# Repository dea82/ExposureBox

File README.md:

# ExposureBox
AVR based exposure box system

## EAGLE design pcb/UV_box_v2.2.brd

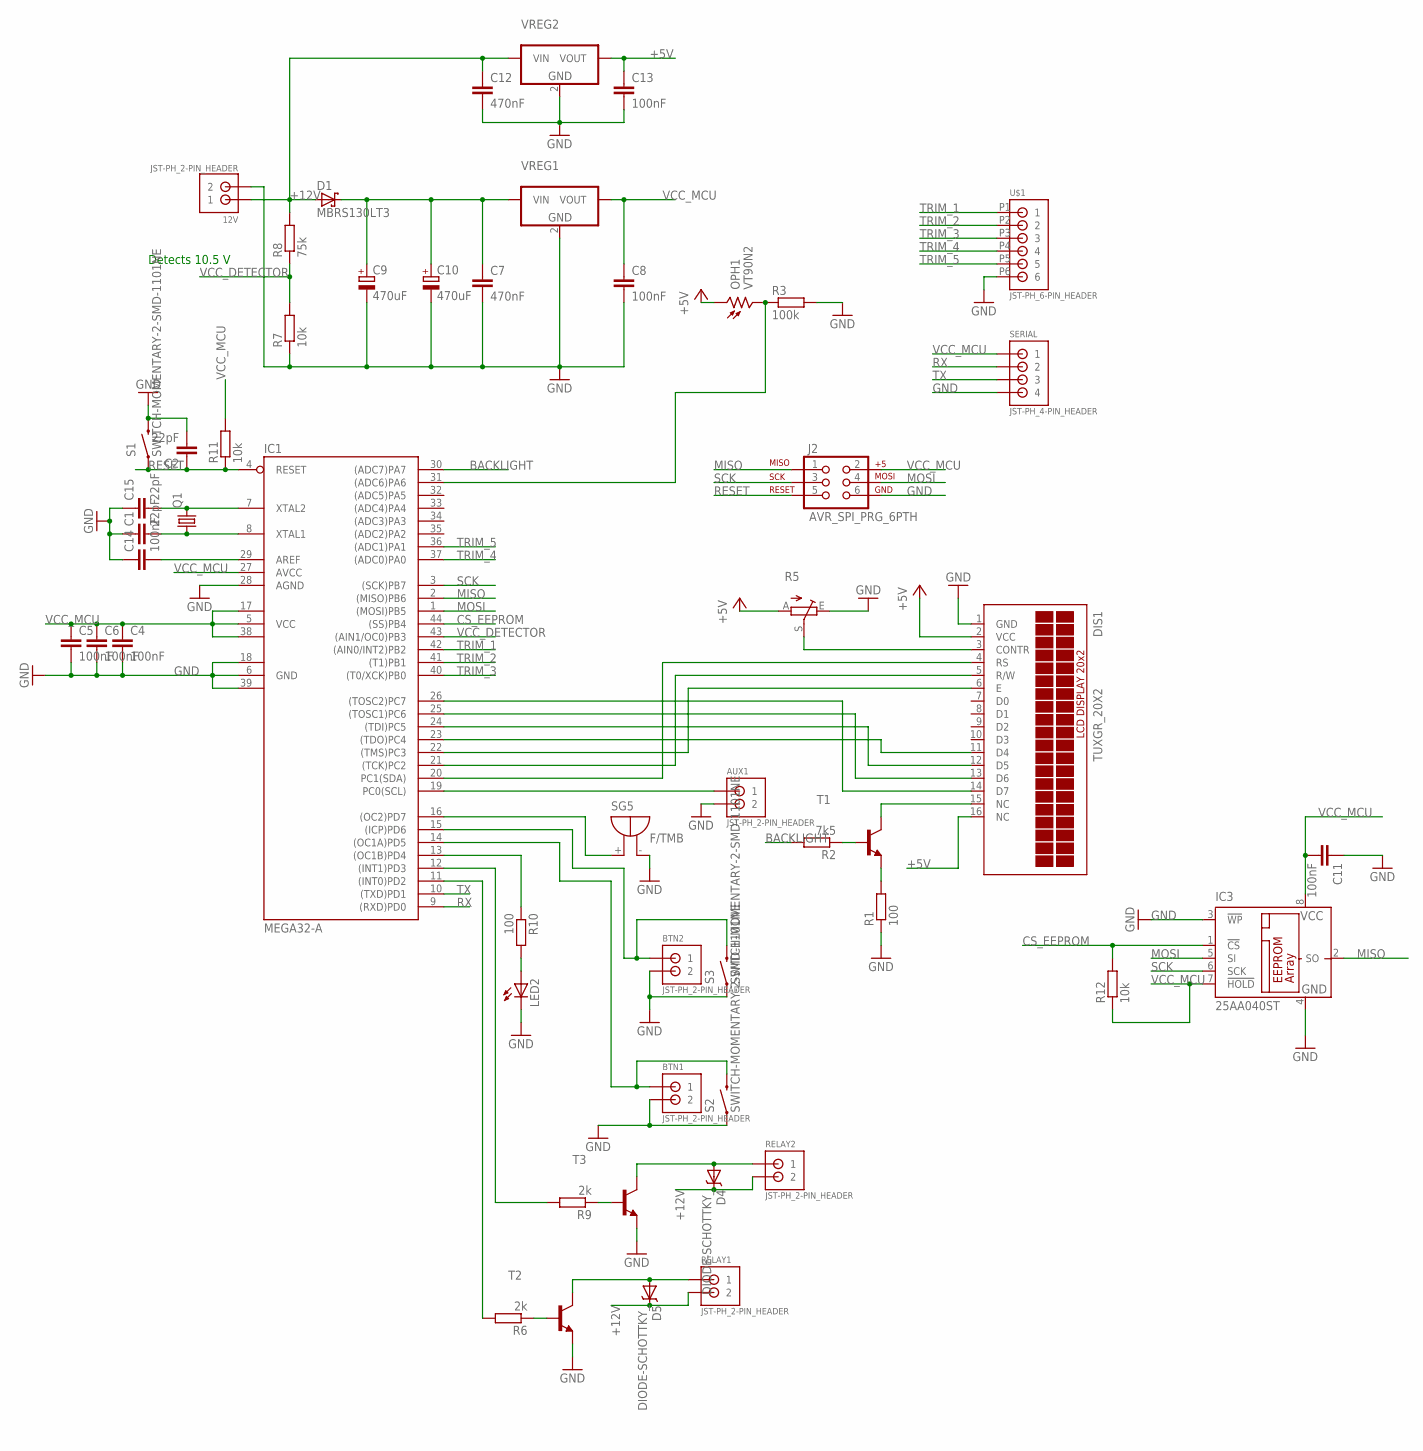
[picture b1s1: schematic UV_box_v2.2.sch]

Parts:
12V: JST-PH_2-PIN_HEADER; JST_B2B-PH_HEADER
AUX1: JST-PH_2-PIN_HEADER; JST_B2B-PH_HEADER
BTN1, BTN2: JST-PH_2-PIN_HEADER; JST_B2B-PH_HEADER
C1, C2, C15: 22pF; C0805
C4, C5, C6, C8, C11, C13, C14: 100nF; C0805
C7, C12: 470nF; C0805
C9, C10: 470uF; 140CLH-0810
D1: MBRS130LT3; SMB
D4, D5: DIODE-SCHOTTKY_; SMA-DIODE
DIS1: TUXGR_20X2
IC1: MEGA32-A; TQFP44
IC3: 25AA040ST; TSSOP8
J2: AVR_SPI_PRG_6PTH; 2X3
LED2: LEDCHIPLED_0805; CHIPLED_0805
OPH1: VT90N2; VT900
Q1: CRYSTALHC49S; HC49/S
R1: 100; R1206
R2: 7k5; R1206
R3: 100k; R1206
R5: TRIM_EU-B25P; B25P
R6, R9: 2k; R1206
R7, R11, R12: 10k; R1206
R8: 75k; R1206
R10: 100; R0805
RELAY1, RELAY2: JST-PH_2-PIN_HEADER; JST_B2B-PH_HEADER
S1, S2, S3: SWITCH-MOMENTARY-2-SMD-1101NE; TACTILE-SWITCH-1101NE
SERIAL: JST-PH_4-PIN_HEADER; JST_B4B-PH_HEADER
SG5: F/TMB
T1, T2, T3: BC847B-NPN-SOT23-BEC; SOT23-BEC
U$1: JST-PH_6-PIN_HEADER; JST_B6B-PH_HEADER
VREG1, VREG2: VREG_3PINS-D2PAK; D2PAK

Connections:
+5V: C13.1, DIS1.2 (VCC), DIS1.16 (NC), OPH1.1, R5.A, VREG2.3 (VOUT)
+12V: 12V.P1 (1), C12.1, D1.A, D4.C, D5.C, R8.2, RELAY1.P2 (2), RELAY2.P2 (2), VREG2.1 (VIN)
BACKLIGHT: IC1.30 ((ADC7)PA7), R2.2
CS_EEPROM: IC1.44 ((SS)PB4), IC3.1 (!CS), R12.2
GND: 12V.P2 (2), AUX1.P2 (2), BTN1.P2 (2), BTN2.P2 (2), C1.1, C2.2, C4.2, C5.2, C6.2, C7.2, C8.2, C9.-, C10.-, C11.1, C12.2, C13.2, C14.1, C15.1, DIS1.1 (GND), IC1.6 (GND), IC1.18 (GND1), IC1.28 (AGND), IC1.39 (GND2), IC3.3 (!WP), IC3.4 (GND), J2.6, LED2.C, R1.1, R3.2, R5.E, R7.1, S1.P$2 (2), S2.P$1 (1), S3.P$1 (1), SERIAL.P4 (4), SG5.-, T2.E, T3.E, U$1.P6 (6), VREG1.2 (GND), VREG2.2 (GND)
MISO: IC1.2 ((MISO)PB6), IC3.2 (SO), J2.1
MOSI: IC1.1 ((MOSI)PB5), IC3.5 (SI), J2.4
unnamed: R1.2, T1.E
unnamed: DIS1.15 (NC), T1.C
unnamed: DIS1.3 (CONTR), R5.S
unnamed: R2.1, T1.B
unnamed: DIS1.4 (RS), IC1.20 (PC1(SDA))
unnamed: DIS1.5 (R/W), IC1.21 ((TCK)PC2)
unnamed: DIS1.6 (E), IC1.22 ((TMS)PC3)
unnamed: C15.2, IC1.7 (XTAL2), Q1.2
unnamed: C1.2, IC1.8 (XTAL1), Q1.1
unnamed: IC1.16 ((OC2)PD7), SG5.+
unnamed: DIS1.11 (D4), IC1.23 ((TDO)PC4)
unnamed: DIS1.12 (D5), IC1.24 ((TDI)PC5)
unnamed: C7.1, C9.+, C10.+, D1.C, VREG1.1 (VIN)
unnamed: DIS1.13 (D6), IC1.25 ((TOSC1)PC6)
unnamed: DIS1.14 (D7), IC1.26 ((TOSC2)PC7)
unnamed: C14.2, IC1.29 (AREF)
unnamed: IC1.31 ((ADC6)PA6), OPH1.2, R3.1
unnamed: AUX1.P1 (1), IC1.19 (PC0(SCL))
unnamed: BTN2.P1 (1), IC1.15 ((ICP)PD6), S3.P$2 (2)
unnamed: BTN1.P1 (1), IC1.14 ((OC1A)PD5), S2.P$2 (2)
unnamed: IC1.11 ((INT0)PD2), R6.2
unnamed: R6.1, T2.B
unnamed: D5.A, RELAY1.P1 (1), T2.C
unnamed: IC1.12 ((INT1)PD3), R9.2
unnamed: R9.1, T3.B
unnamed: D4.A, RELAY2.P1 (1), T3.C
unnamed: IC1.13 ((OC1B)PD4), R10.1
unnamed: LED2.A, R10.2
RESET: C2.1, IC1.4 (RESET), J2.5, R11.1, S1.P$1 (1)
RX: IC1.9 ((RXD)PD0), SERIAL.P2 (2)
SCK: IC1.3 ((SCK)PB7), IC3.6 (SCK), J2.3
TRIM_1: IC1.42 ((AIN0/INT2)PB2), U$1.P1 (1)
TRIM_2: IC1.41 ((T1)PB1), U$1.P2 (2)
TRIM_3: IC1.40 ((T0/XCK)PB0), U$1.P3 (3)
TRIM_4: IC1.37 ((ADC0)PA0), U$1.P4 (4)
TRIM_5: IC1.36 ((ADC1)PA1), U$1.P5 (5)
TX: IC1.10 ((TXD)PD1), SERIAL.P3 (3)
VCC_DETECTOR: IC1.43 ((AIN1/OC0)PB3), R7.2, R8.1
VCC_MCU: C4.1, C5.1, C6.1, C8.1, C11.2, IC1.5 (VCC), IC1.17 (VCC1), IC1.27 (AVCC), IC1.38 (VCC2), IC3.7 (!HOLD), IC3.8 (VCC), J2.2, R11.2, R12.1, SERIAL.P1 (1), VREG1.3 (VOUT)

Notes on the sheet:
Detects 10.5 V

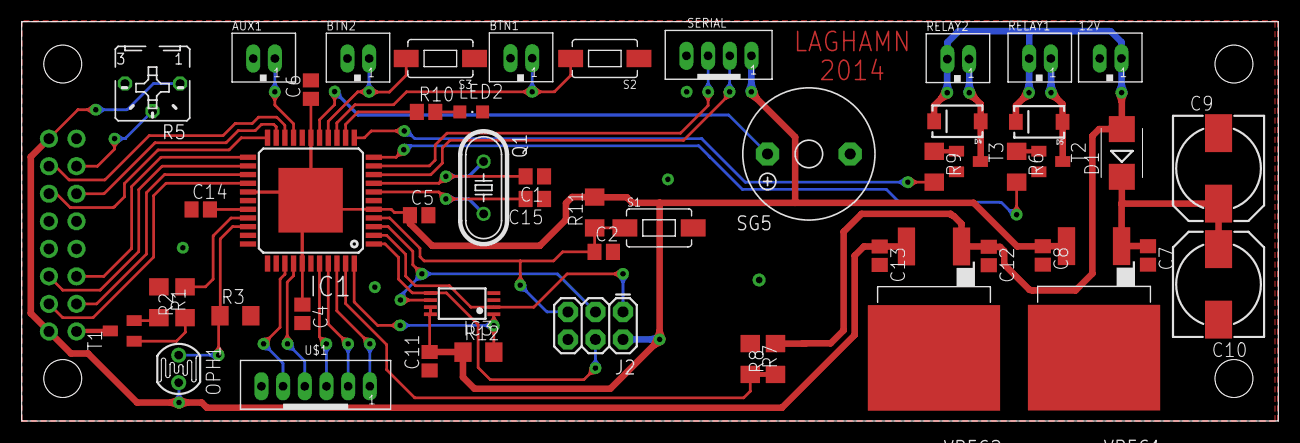
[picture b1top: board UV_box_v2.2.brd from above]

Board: 2 copper layers, 115.9 x 36.8 mm, 52 parts (1 on the bottom side), 46 nets.

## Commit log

2015-03-26 First update.
2015-04-01 Updates within statistics and data storage.
2015-04-04 Updated data storage algorithms.
2015-04-08 Update before removing enumerated type and replace it with number of bytes.
2015-04-25 - Updates of data storage. - Removed unused files.
2015-04-26 Changed project name.
2015-05-09 Update serial module with char type argument for serial string output.
2015-07-22 Added pcbs.
2015-08-21 Made huge progress of the eeprom verification.
2015-08-21 This closes #4: Bug in butt.c
    Task-Url: http://github.com/dea82/ExposureBox/issues/issue/4
2015-08-21 Fixes #5: Replace Util_safeInc... with macro from AVR-HVSP which is much more space optimized
    Task-Url: http://github.com/dea82/ExposureBox/issues/issue/5
2015-08-21 Fixes #2: First ADC conversion may be wrong when using internal bandgap
    Task-Url: http://github.com/dea82/ExposureBox/issues/issue/2
2015-08-21 Fixes #3: Check WDT-reset
    Task-Url: http://github.com/dea82/ExposureBox/issues/issue/3
2015-08-21 Fixes #6: Implement data storage copy function
    Task-Url: http://github.com/dea82/ExposureBox/issues/issue/6
2015-08-25 Updates of data storage.
2015-08-28 Updates on data storage and statisitics.
2015-10-15 Setting up travis.
2015-10-18 General update.
2015-10-20 Added makefiles.
2015-10-20 no message
2015-10-20 Testar feature branch.
2015-10-22 Created files.
2015-10-26 Changed makefile script.
2015-10-26 Delete .travis.yml
    Tar nu bort bygg check.
2015-11-11 Create Makefile
2015-11-11 Update Makefile

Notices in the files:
parts and their libraries:
SparkFun-Connectors: Licensing: CC v3.0 Share-Alike You are welcome to use this library for commercial purposes.
